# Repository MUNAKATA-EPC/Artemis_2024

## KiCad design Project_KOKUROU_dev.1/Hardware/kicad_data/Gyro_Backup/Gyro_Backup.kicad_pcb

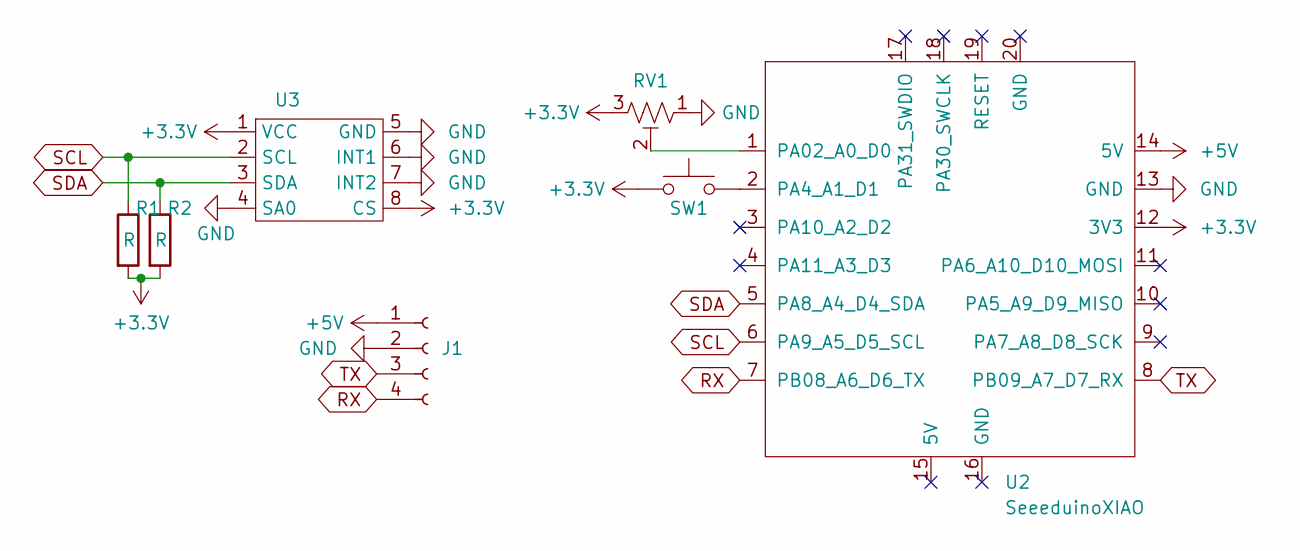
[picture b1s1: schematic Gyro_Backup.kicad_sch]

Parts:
J1: Conn_01x04_Socket; JST_XH_S4B-XH-A_1x04_P2.50mm_Horizontal
R1, R2: R; R_Axial_DIN0204_L3.6mm_D1.6mm_P5.08mm_Horizontal
RV1: R_Potentiometer_Trim_US; Potentiometer_Vishay_T73YP_Vertical
SW1: SW_Push; SW_PUSH_6mm
U2: SeeeduinoXIAO; seeeduinoXIAO
U3: L3GD20H_Module

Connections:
+3.3V: R1.2, R2.2, RV1.3, SW1.1, U2.12 (3V3), U3.1 (VCC), U3.8 (CS)
+5V: J1.1, U2.14 (5V)
GND: J1.2, RV1.1, U2.13 (GND), U3.4 (SA0), U3.5 (GND), U3.6 (INT1), U3.7 (INT2)
unnamed: RV1.2, U2.1 (PA02_A0_D0)
unnamed: SW1.2, U2.2 (PA4_A1_D1)
RX: J1.4, U2.7 (PB08_A6_D6_TX)
SCL: R1.1, U2.6 (PA9_A5_D5_SCL), U3.2 (SCL)
SDA: R2.1, U2.5 (PA8_A4_D4_SDA), U3.3 (SDA)
TX: J1.3, U2.8 (PB09_A7_D7_RX)

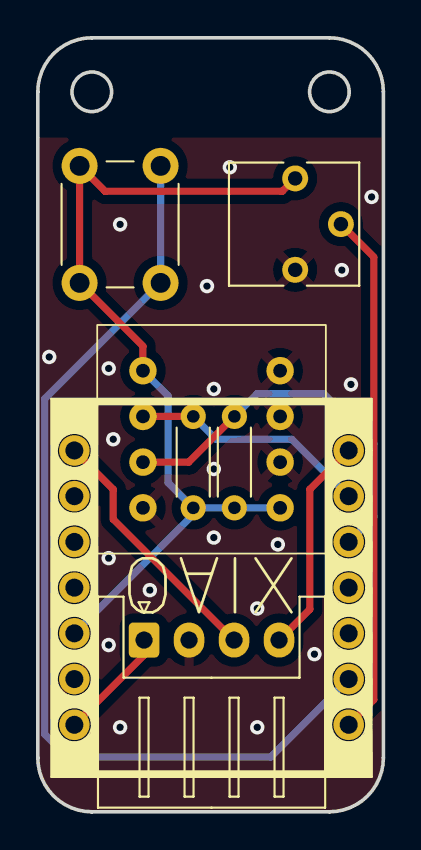
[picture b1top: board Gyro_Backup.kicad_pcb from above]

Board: 2 copper layers, 19.2 x 43.0 mm, 7 parts (0 on the bottom side), 9 nets.

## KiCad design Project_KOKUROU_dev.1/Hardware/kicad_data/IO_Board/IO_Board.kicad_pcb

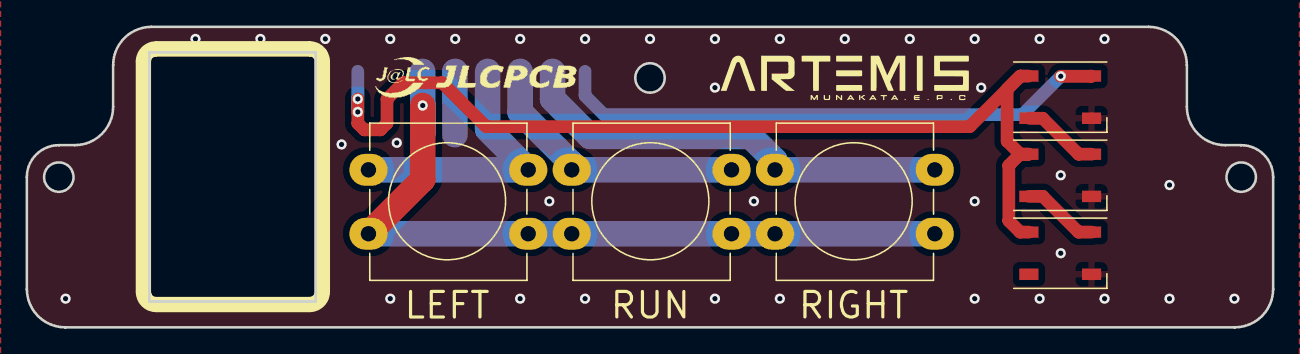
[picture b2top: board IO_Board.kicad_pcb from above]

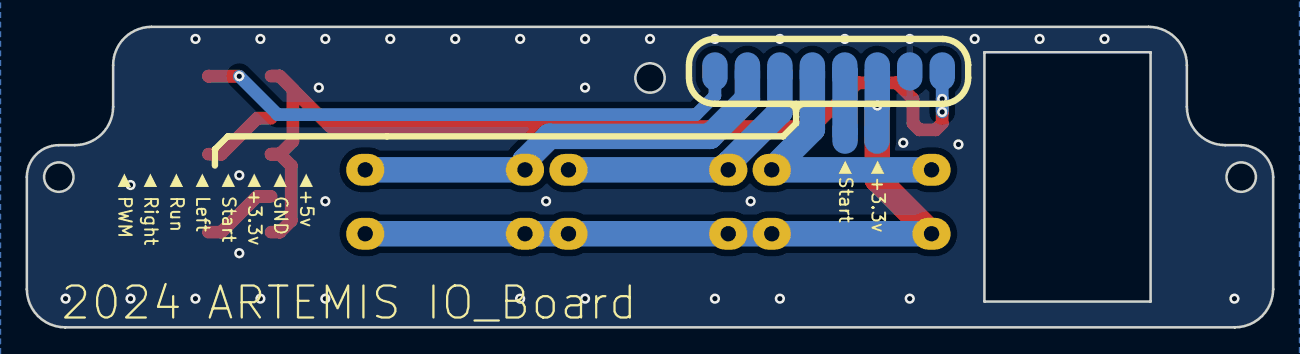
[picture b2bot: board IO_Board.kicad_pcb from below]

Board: 2 copper layers, 97.5 x 23.5 mm, 8 parts (2 on the bottom side), 10 nets.

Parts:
D1, D2, D3: WS2812B; LED_WS2812B_PLCC4_5.0x5.0mm_P3.2mm
J1: Conn_01x08_Socket; PinHeader_1x08_P2.54mm_Vertical
LEFT: SW_Push; SW_PUSH-12mm_Wuerth-430476085716
RIGHT: SW_Push; SW_PUSH-12mm_Wuerth-430476085716
RUN: SW_Push; SW_PUSH-12mm_Wuerth-430476085716
SW4: SW_DIP_x01; JST_XH_B2B-XH-A_1x02_P2.50mm_Vertical

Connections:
+3.3V: J1.3, LEFT.1, RIGHT.1, RUN.1
+5V: D1.1 (VDD), D2.1 (VDD), D3.1 (VDD), J1.1
BTN_Left: J1.5, LEFT.2
BTN_Right: J1.7, RIGHT.2
BTN_Run: J1.6, RUN.2
GND: D1.3 (VSS), D2.3 (VSS), D3.3 (VSS), J1.2
IND_PWM: D1.4 (DIN), J1.8
unnamed: D1.2 (DOUT), D2.4 (DIN)
unnamed: D2.2 (DOUT), D3.4 (DIN)
SWT_Start: J1.4, SW4.2

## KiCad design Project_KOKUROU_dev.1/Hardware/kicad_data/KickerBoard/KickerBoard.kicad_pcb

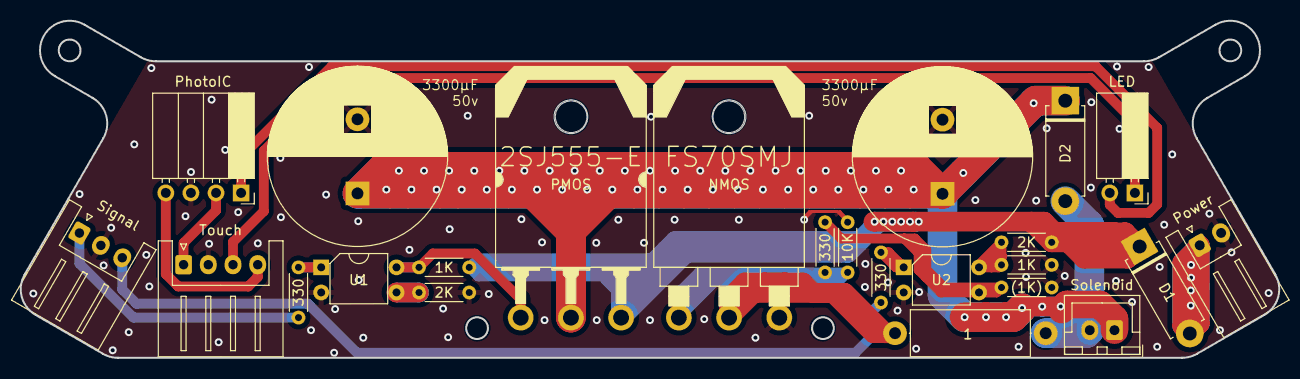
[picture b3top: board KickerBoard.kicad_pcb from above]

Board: 2 copper layers, 127.3 x 34.1 mm, 24 parts (0 on the bottom side), 19 nets.

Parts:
1: 1; R_Axial_DIN0414_L11.9mm_D4.5mm_P15.24mm_Horizontal
1K, 1K#2: 1K; R_Axial_DIN0204_L3.6mm_D1.6mm_P5.08mm_Horizontal
2K, 2K#2: 2K; R_Axial_DIN0204_L3.6mm_D1.6mm_P5.08mm_Horizontal
10K: 10K; R_Axial_DIN0204_L3.6mm_D1.6mm_P5.08mm_Horizontal
330, 330#2, 330#3: 330; R_Axial_DIN0204_L3.6mm_D1.6mm_P5.08mm_Horizontal
(1K): 1K; R_Axial_DIN0204_L3.6mm_D1.6mm_P5.08mm_Horizontal
C1, C2: C; CP_Radial_D18.0mm_P7.50mm
D1, D2: D; D_5W_P10.16mm_Horizontal
LED: Conn_01x02_Socket; PinSocket_1x02_P2.54mm_Horizontal
NMOS: NMOS; FS70SMJ
PMOS: PMOS; FS70SMJ
PhotoIC: Conn_01x04_Socket; PinSocket_1x04_P2.54mm_Horizontal
Power: Conn_01x02_Socket; JST_XH_S2B-XH-A_1x02_P2.50mm_Horizontal
Signal: Conn_01x03_Socket; JST_XH_S3B-XH-A_1x03_P2.50mm_Horizontal
Solenoid: Conn_01x02_Socket; JST_XH_B2B-XH-A_1x02_P2.50mm_Vertical
Touch: Conn_01x04_Socket; JST_XH_S4B-XH-A_1x04_P2.50mm_Horizontal
U1, U2: EL817; DIP-4_W7.62mm

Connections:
+3.3V: PhotoIC.2, Touch.1
+15V: 1K.2, 2K#2.1, U2.4
+48V: 1K#2.1, 2K#2.2, D1.1 (K), PMOS.3 (S)
FET1: 330#2.1, Signal.1
FET2: 330#3.1, Signal.3
GND: 1K.1, 2K.2, 10K.2, (1K).1, C1.2, C2.2, NMOS.3 (S), PhotoIC.3, Power.2, Signal.2, Touch.2, U1.2, U2.2
K: LED.2, PhotoIC.1
LED: LED.1, Touch.3
unnamed: D1.2 (A), Power.1
unnamed: 1K#2.2, PMOS.2 (G), U1.4
unnamed: 1.2, NMOS.1 (D)
unnamed: 10K.1, 330.2, NMOS.2 (G)
unnamed: 330#2.2, U1.1
unnamed: 330#3.2, U2.1
unnamed: 330.1, (1K).2, U2.3
unnamed: 2K.1, U1.3
Solenoid+: C1.1, C2.1, D2.1 (K), PMOS.1 (D), Solenoid.1
Solenoid-: 1.1, D2.2 (A), Solenoid.2
Touch: PhotoIC.4, Touch.4

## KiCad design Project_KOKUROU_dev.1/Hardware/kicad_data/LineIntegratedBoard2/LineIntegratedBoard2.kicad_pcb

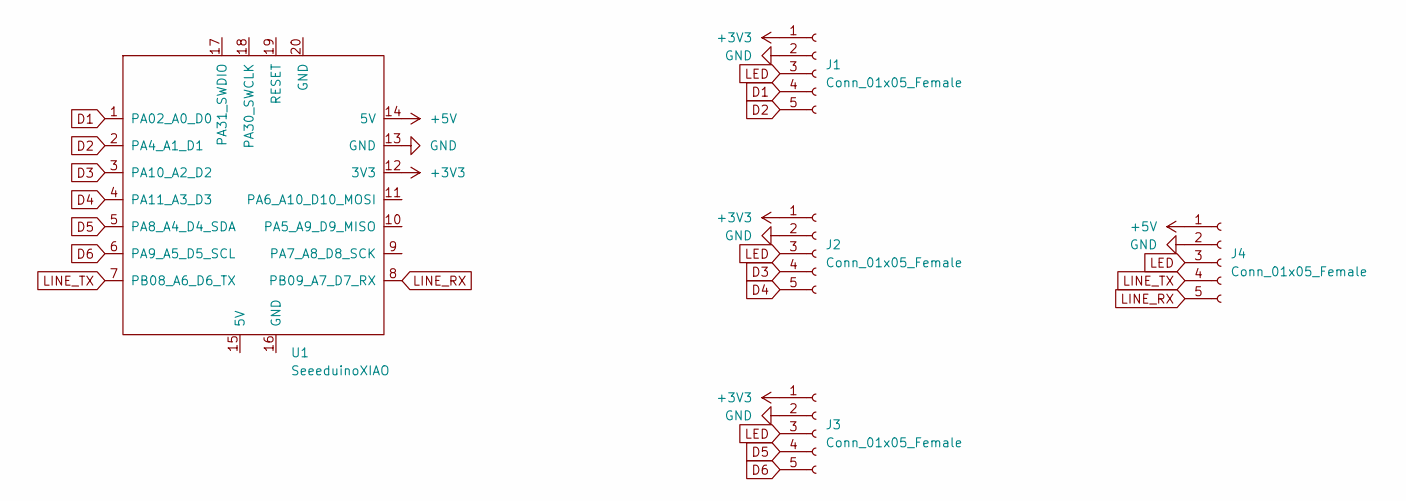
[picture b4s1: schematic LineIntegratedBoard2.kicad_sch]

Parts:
J1, J2, J3, J4: Conn_01x05_Female; PinSocket_1x05_P2.54mm_Horizontal
U1: SeeeduinoXIAO; Seeeduino XIAO-MOUDLE14P-2.54-21X17.8MM

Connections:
+3V3: J1.1, J2.1, J3.1, U1.12 (3V3)
+5V: J4.1, U1.14 (5V)
D1: J1.4, U1.1 (PA02_A0_D0)
D2: J1.5, U1.2 (PA4_A1_D1)
D3: J2.4, U1.3 (PA10_A2_D2)
D4: J2.5, U1.4 (PA11_A3_D3)
D5: J3.4, U1.5 (PA8_A4_D4_SDA)
D6: J3.5, U1.6 (PA9_A5_D5_SCL)
GND: J1.2, J2.2, J3.2, J4.2, U1.13 (GND)
LED: J1.3, J2.3, J3.3, J4.3
LINE_RX: J4.5, U1.8 (PB09_A7_D7_RX)
LINE_TX: J4.4, U1.7 (PB08_A6_D6_TX)

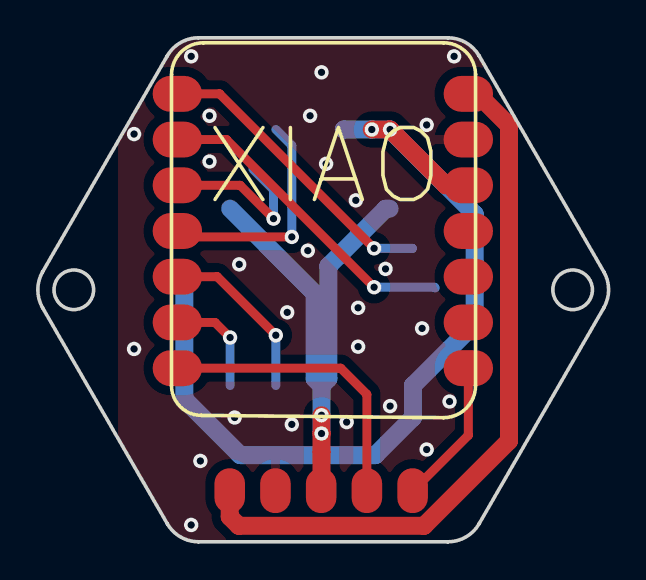
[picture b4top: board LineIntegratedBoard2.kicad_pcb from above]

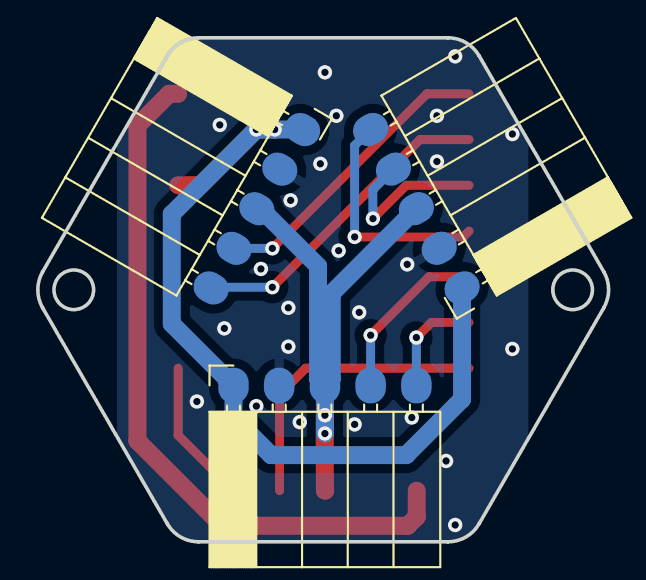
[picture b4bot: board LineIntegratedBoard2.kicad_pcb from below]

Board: 2 copper layers, 31.7 x 28.0 mm, 5 parts (3 on the bottom side), 12 nets.

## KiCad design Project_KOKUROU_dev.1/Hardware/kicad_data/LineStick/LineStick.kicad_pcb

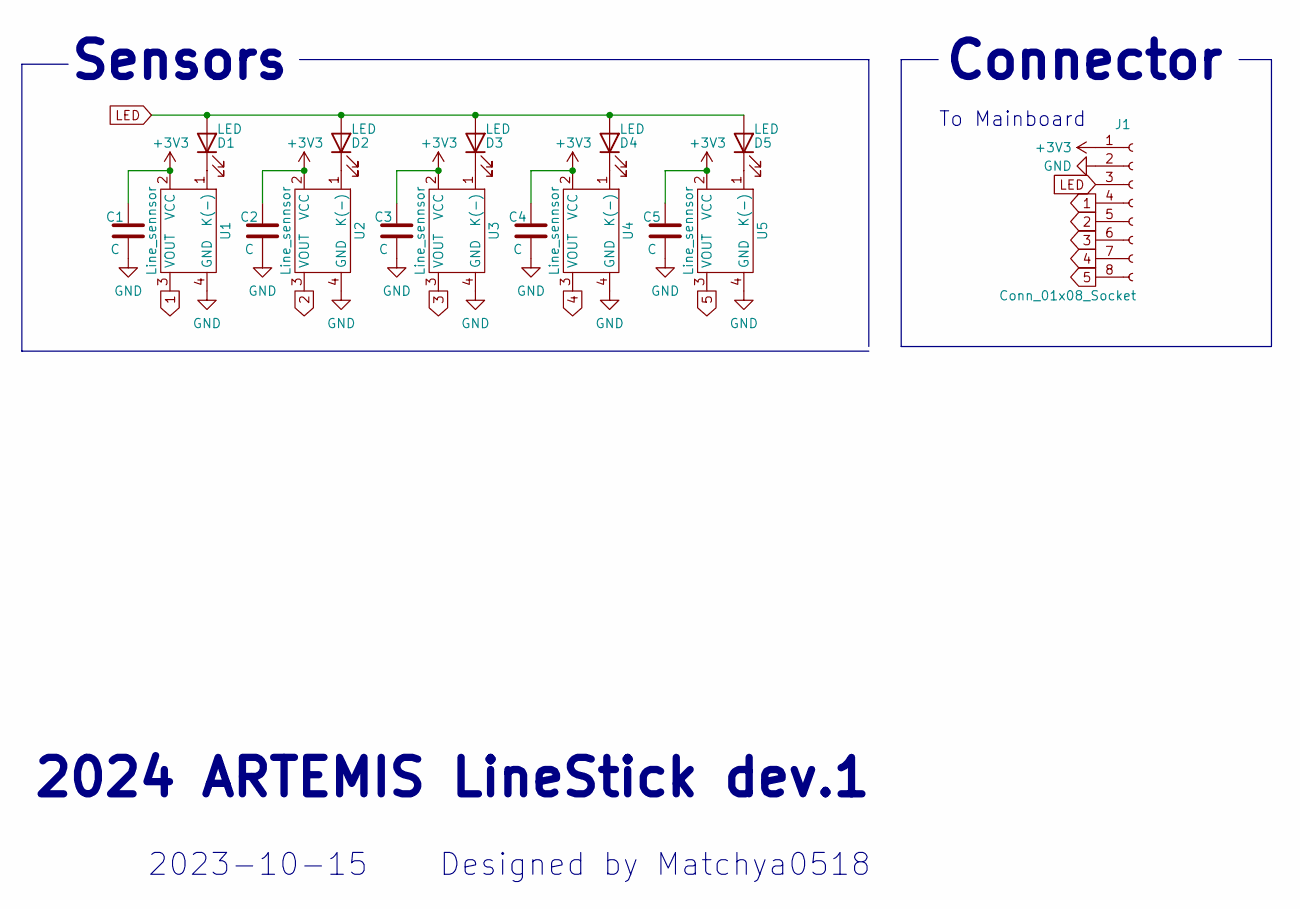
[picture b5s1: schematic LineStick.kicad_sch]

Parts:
C1, C2, C3, C4, C5: C
D1, D2, D3, D4, D5: LED
J1: Conn_01x08_Socket
U1, U2, U3, U4, U5: Line_sennsor

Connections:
1: J1.4, U1.3 (VOUT)
2: J1.5, U2.3 (VOUT)
3: J1.6, U3.3 (VOUT)
4: J1.7, U4.3 (VOUT)
5: J1.8, U5.3 (VOUT)
+3V3: C1.1, C2.1, C3.1, C4.1, C5.1, J1.1, U1.2 (VCC), U2.2 (VCC), U3.2 (VCC), U4.2 (VCC), U5.2 (VCC)
GND: C1.2, C2.2, C3.2, C4.2, C5.2, J1.2, U1.4 (GND), U2.4 (GND), U3.4 (GND), U4.4 (GND), U5.4 (GND)
LED: D1.2 (A), D2.2 (A), D3.2 (A), D4.2 (A), D5.2 (A), J1.3
unnamed: D1.1 (K), U1.1 (K(-))
unnamed: D2.1 (K), U2.1 (K(-))
unnamed: D3.1 (K), U3.1 (K(-))
unnamed: D4.1 (K), U4.1 (K(-))
unnamed: D5.1 (K), U5.1 (K(-))

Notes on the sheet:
Designed by Matchya0518
Sensors
2023-10-15
2024 ARTEMIS LineStick dev.1
To Mainboard
Connector

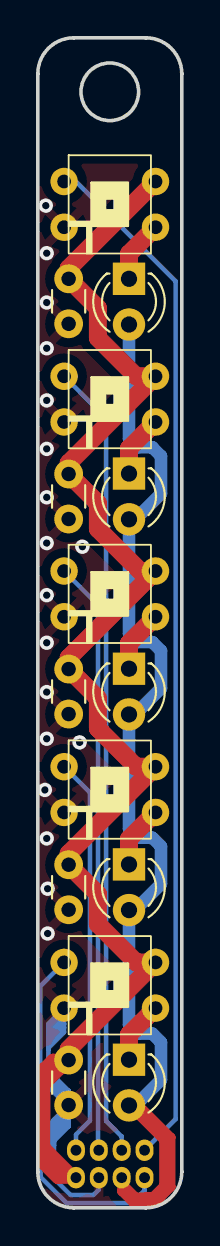
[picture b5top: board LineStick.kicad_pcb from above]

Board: 2 copper layers, 8.0 x 65.0 mm, 16 parts (0 on the bottom side), 13 nets.

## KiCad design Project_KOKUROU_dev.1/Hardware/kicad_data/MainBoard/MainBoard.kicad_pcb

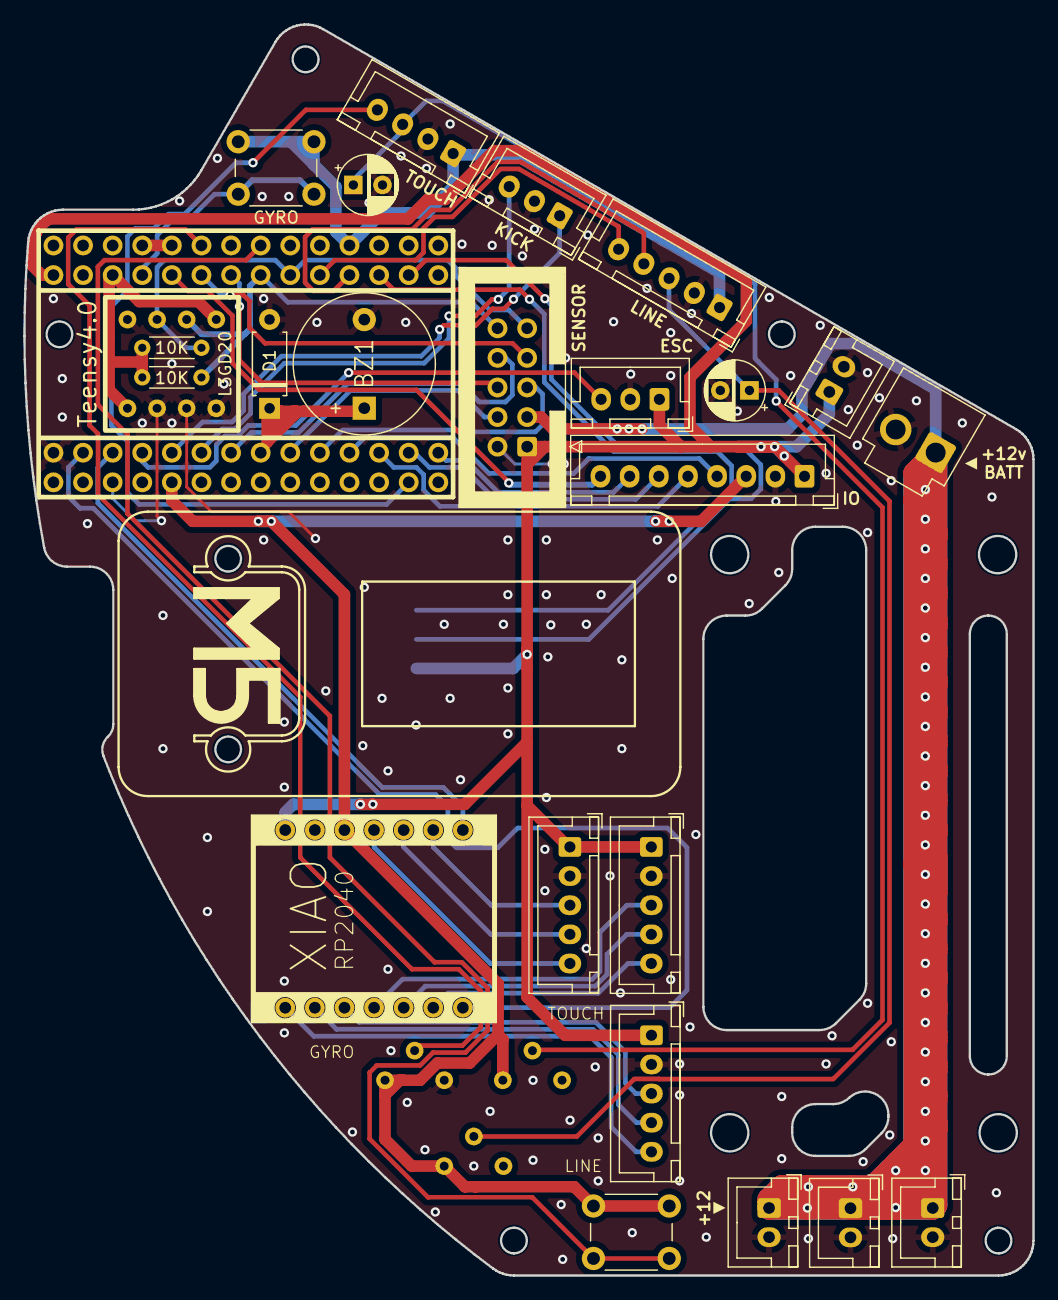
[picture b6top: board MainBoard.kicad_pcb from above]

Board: 2 copper layers, 86.6 x 107.3 mm, 29 parts (1 on the bottom side), 41 nets.

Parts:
10K, 10K#2: R; R_Axial_DIN0204_L3.6mm_D1.6mm_P5.08mm_Horizontal
BZ1: Buzzer; Buzzer_12x9.5RM7.6
C1, C2: C; CP_Radial_D5.0mm_P2.50mm
D1: D; D_A-405_P7.62mm_Horizontal
ESC: Conn_01x03_Socket; JST_XH_B3B-XH-A_1x03_P2.50mm_Vertical
GYRO: SW_Push; SW_PUSH_6mm_H5mm
GYRO#2: R_Potentiometer_Trim_US; 可変抵抗
IO: Conn_01x08_Socket; JST_XH_B8B-XH-A_1x08_P2.50mm_Vertical
J1, J2, J3: Conn_01x05_Socket; JST_XH_B5B-XH-A_1x05_P2.50mm_Vertical
J4, J5, J6, J12: Conn_01x02_Socket; JST_XH_B2B-XH-A_1x02_P2.50mm_Vertical
J7: Conn_01x04_Socket; JST_XH_S4B-XH-A_1x04_P2.50mm_Horizontal
J11: Conn_01x02_Socket; JST_VH_B2P-VH-B_1x02_P3.96mm_Vertical
KICK: Conn_01x03_Socket; JST_XH_B3B-XH-A_1x03_P2.50mm_Vertical
LINE: Conn_01x05_Socket; JST_XH_B5B-XH-A_1x05_P2.50mm_Vertical
LINE#2: R_Trim; 可変抵抗
SENSOR: Conn_01x10_Socket; IDC-Header_2x05_P2.54mm_Vertical
SW2: SW_Push; SW_PUSH_6mm_H5mm
TOUCH: Conn_01x04_Socket; JST_XH_B4B-XH-A_1x04_P2.50mm_Vertical
TOUCH#2: R_Trim; 可変抵抗
U1: Teensy4.0; Teensy_Brakeout
U2: SeeeduinoXIAO; seeeduinoXIAO
U3: L3GD20H_Module_KiCad6.0

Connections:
+3.3V: 10K.2, 10K#2.2, GYRO.2, GYRO#2.1, IO.3, LINE.1, LINE#2.1, SW2.2, TOUCH.1, TOUCH#2.1, U1.31 (3V3), U2.12 (3V3), U3.1 (VCC), U3.8 (CS)
+5V: ESC.1, IO.1, J1.1, J2.1, J3.1, J7.2, J12.1, SENSOR.1, U1.33 (VIN), U2.14 (5V)
+12V: J4.1, J5.1, J6.1, J11.1, SENSOR.3
BLDC_PWM: ESC.3, U1.4 (2_OUT2)
BTN_EX: SW2.1, U1.37 (26_A12_MOSI1)
BTN_Left: IO.5, U1.12 (10_CS_MQSR)
BTN_Right: IO.7, U1.14 (12_MISO_MQSL)
BTN_Run: IO.6, U1.13 (11_MOSI_CTX1)
Buzzer: BZ1.1 (-), D1.1 (K), U1.8 (6_OUT1D)
CAM_RX: SENSOR.7, U1.28 (21_A7_RX5_BCLK1)
CAM_TX: SENSOR.6, U1.27 (20_A6_TX5_LRCLK1)
FET1_Digital: KICK.1, U1.5 (3_LRCLK2)
FET2_Digital: KICK.3, U1.6 (4_BCLK2)
GND: BZ1.2 (+), C1.2, C2.2, D1.2 (A), ESC.2, GYRO#2.3, IO.2, J1.2, J2.2, J3.2, J4.2, J5.2, J6.2, J7.1, J11.2, J12.2, KICK.2, LINE.2, SENSOR.2, TOUCH.2, U1.1 (GND), U2.13 (GND), U3.4 (SA0), U3.5 (GND), U3.6 (INT1), U3.7 (INT2)
IMU_RX: J7.4, U1.22 (15_A1_RX3_SPDIF_IN)
IMU_TX: J7.3, U1.21 (14_A0_TX3_SPDIF_OUT)
IND_PWM: IO.8, U1.29 (22_A8_CTX1)
IR_RX: SENSOR.4, U1.9 (7_RX2_OUT1A)
IR_TX: SENSOR.5, U1.10 (8_TX2_IN1)
L3GD_RST: GYRO.1, U1.30 (23_A9_CRX1_MCLK1)
L3GD_SCL: 10K.1, SENSOR.10, U1.26 (19_A5_SCL0), U3.2 (SCL)
L3GD_SDA: 10K#2.1, SENSOR.9, U1.25 (18_A4_SDA0), U3.3 (SDA)
L3GD_Trim: GYRO#2.2, U1.38 (27_A13_SCK1)
LINE_RX: LINE.4, U1.23 (16_A2_RX4_SCL1)
LINE_TX: LINE.5, U1.24 (17_A3_TX4_SDA1)
MD1_INA: J1.3, U2.3 (PA10_A2_D2)
MD1_INB: J1.4, U2.2 (PA4_A1_D1)
MD1_PWM: J1.5, U2.1 (PA02_A0_D0)
MD2_INA: J2.3, U2.4 (PA11_A3_D3)
MD2_INB: J2.4, U2.5 (PA8_A4_D4_SDA)
MD2_PWM: J2.5, U2.6 (PA9_A5_D5_SCL)
MD3_INA: J3.3, U2.9 (PA7_A8_D8_SCK)
MD3_INB: J3.4, U2.10 (PA5_A9_D9_MISO)
MD3_PWM: J3.5, U2.11 (PA6_A10_D10_MOSI)
MD_RX: U1.2 (0_RX1_CRX2_CS1), U2.7 (PB08_A6_D6_TX)
MD_TX: U1.3 (1_TX1_CTX2_MISO1), U2.8 (PB09_A7_D7_RX)
NeoPixel_PWM: SENSOR.8, U1.7 (5_IN2)
unnamed: C2.1, TOUCH.3, TOUCH#2.2
unnamed: C1.1, LINE.3, LINE#2.2
SWT_START: IO.4, U1.11 (9_OUT1C)
Touch: TOUCH.4, U1.41 (30_CRX3)
